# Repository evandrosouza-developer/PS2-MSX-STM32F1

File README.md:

# STM32: PS/2 to USB Converter

This code facilitates a STM32 chip to convert between PS/2 and MSX computer. It is meant to connect a keyboard, which only provides a PS/2 connector, to a MSX (or any one that have a up to 15 active columns and reads zeroes througth 8 bits - up to 15 x 8 matrix) computer.
This code powers and has been tested on the following Windows keyboards with brazilian 275 layout:
- Compaq RT235BTWBR;
- Clone KE11090749;
- Clone #09100.

The original code was originally developed based on:
- Cherry G80-3000LSMDE;

## Dependencies

- `arm-none-eabi-gcc`
- `arm-none-eabi-gdb`
- `arm-none-eabi-binutils`
- `arm-none-eabi-newlib`
- `stlink`
- `openocd (if you wnat to debug)`
- `mpfr`

## Preparations

After cloning the repository you need to make the following preparations:

```
git submodule init
git submodule update
cd libopencm3
make
cd ..
make
```

## Hardware and Setup

You will obviously need a STM32F103C8T6 chip. I have used a chinese blue pill. The software was made thinking in use of compatible processors, like GD32 for example. The software was made considering 8.000Mhz oscillator crystal, to clock the STM32F103C8T6 microcontroller chip at 72MHz. The connections are:

1) PS/2 Keyboard:
- Clock Pin PA12 - Connect to PS/2 mini-din 45322 pin 5 throught R16;
- Data Pin PA9 - Connect to PS/2 mini-din pin 1 throught R18;
- +5V PS/2 power - Connect collector of Q2 to mini-din pin 4;
- GND - Connect GNDD (Digital Ground) to mini-din pin 3.

2) MSX computer:
Obs.: You have to access PPI Ports B0 to B7 (Lines X0 to X7), Port C0 to C3 (Y0 to Y3), Port C6 (Caps Lock, pin 11 of DIP package), and for Russian and Japanese Computers (Cyrillic and Kana alphabets), you have to get access to YM2149 IOB7, pin 6 of DIP package.
- Y3 - Connect to MSX PPI 8255 Signal PC3;
- Y2 - Connect to MSX PPI 8255 Signal PC2;
- Y1 - Connect to MSX PPI 8255 Signal PC1;
- Y0 - Connect to MSX PPI 8255 Signal PC0;
- X7 - Connect to MSX PPI 8255 Signal PB7 (Hotbit HB-8000 CI-15 Pin 25);
- X6 - Connect to MSX PPI 8255 Signal PB6 (Hotbit HB-8000 CI-15 Pin 24);
- X5 - Connect to MSX PPI 8255 Signal PB5 (Hotbit HB-8000 CI-15 Pin 23);
- X4 - Connect to MSX PPI 8255 Signal PB4 (Hotbit HB-8000 CI-15 Pin 22);
- X3 - Connect to MSX PPI 8255 Signal PB3 (Hotbit HB-8000 CI-15 Pin 21);
- X2 - Connect to MSX PPI 8255 Signal PB2 (Hotbit HB-8000 CI-15 Pin 20);
- X1 - Connect to MSX PPI 8255 Signal PB1 (Hotbit HB-8000 CI-15 Pin 19);
- X0 - Connect to MSX PPI 8255 Signal PB0 (Hotbit HB-8000 CI-15 Pin 18);
- Caps LED - Connect to MSX PPI 8255 Signal PC6 (Hotbit HB-8000 CI-15 Pin 11 / Expert XP-800 CI-4);
- Kana LED - Connect to MSX YM2149 IOB7, pin 6 of DIP package. If the MSX doesn't have this, you can leave it open, as it already has an internal pull-up connection.

3) Serial connection: Needed only to update internal PS/2 to MSX key mapping Database. To create this Intel Hex file, better to use the Macro based Excel file, so you have to trust and enable macro excecution in excel app.
The structure of the Database is:
	The  three first columns of each line are the mapped scan codes;
	The 4th column is The Control Byte, detailed bellow:
	CONTROL BYTE:
		High nibble is Reserved;
		(bit 3) Combined Shift;
		(bit 2) Reserved-Not used;
		(bits 1-0) Modifyer Type:
		.0 - Default mapping
		.1 - NumLock Status+Shift changes
		.2 - PS/2 Shift
		.3 - Reserved-Not used
	
	This table has 3 modifyers: Up two MSX keys are considered to each mapping behavior modifying:
	
	5th and 6th columns have the mapping ".0 - Default mapping";
	7th e 8th columns have the mapping ".1 - NumLock Status+Shift changes";
	9th and 10th columns have the mapping ".2 - PS/2 Shift", where I need to
	release the sinalized Shift in PS/2 to the MSX and put the coded key, and so,
	release them, reapplying the Shift key, deppending on the initial state;

	Each column has a MSX coded key, with the sollwing structure:
	(Bit 7:4) MSX Y PPI 8255 PC3:0 is send to an OC outputs BCD decoder, for example:
					 In the case of Hotbit HB8000, the keyboard scan is done as a 9 columns scan, CI-16 7445N 08 to 00;
					 If equals to 1111 (Y=15), there is no MSX key mapped.
	(Bit 3)	 		 0: keypress
					 1: key release;
	(Bit 2:0) MSX X, ie, which bit will carry the key, to be read by PPI 8255 PB7:0.

Use a ST-Link v2 Programmer (or similar) to flash the program using `make flash` onto the STM32.

# PS2-MSX-STM32F1
# PS2-MSX-STM32F1

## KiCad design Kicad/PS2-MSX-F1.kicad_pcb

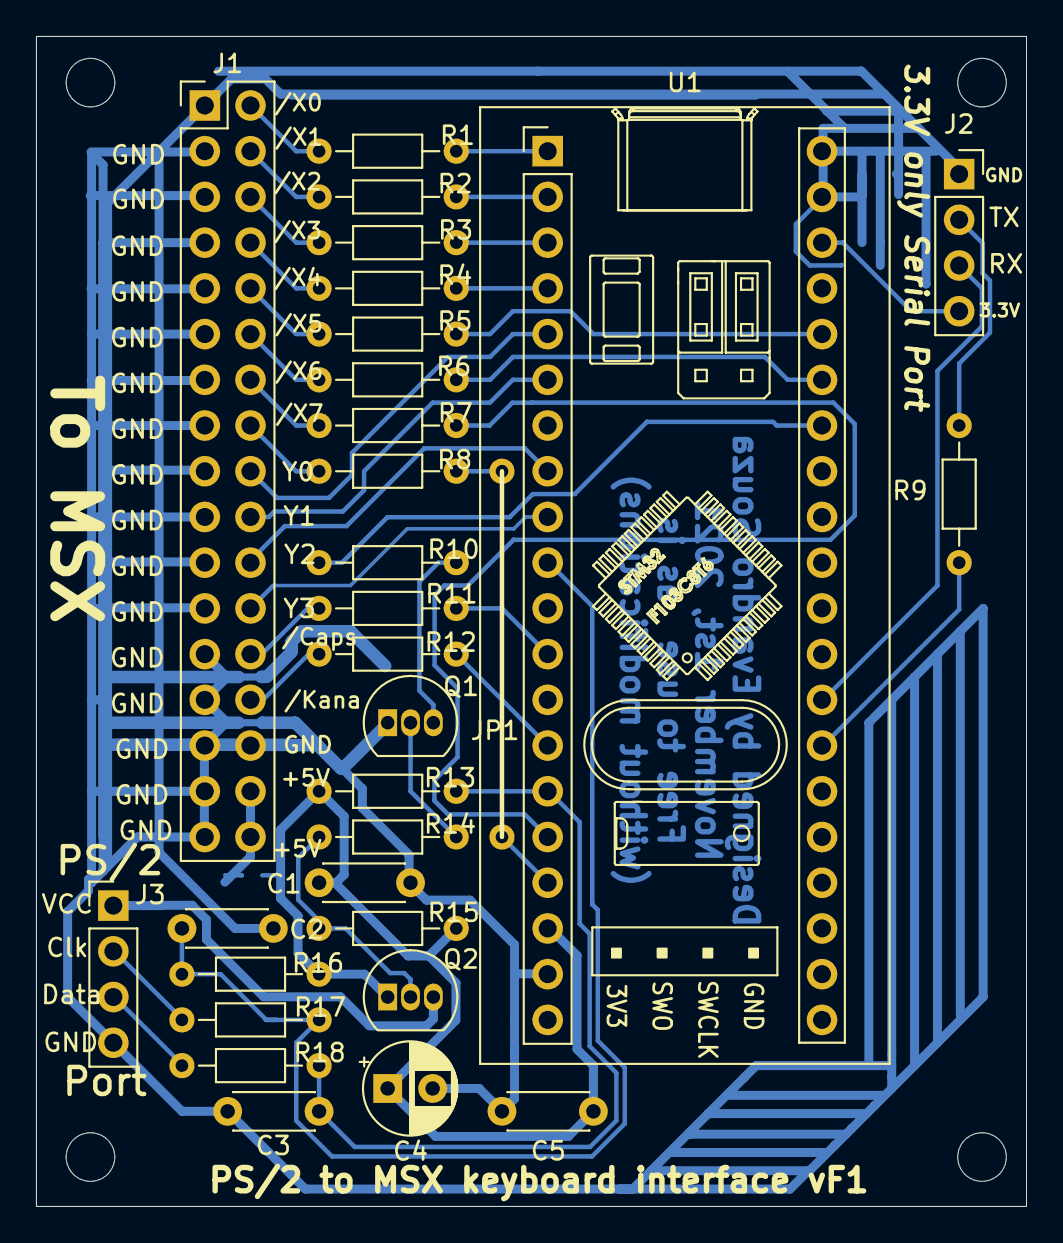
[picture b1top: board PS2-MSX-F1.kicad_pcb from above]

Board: 2 copper layers, 55.0 x 65.0 mm, 31 parts (1 on the bottom side), 41 nets.

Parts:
C1, C5: 100nF; C_Disc_D4.3mm_W1.9mm_P5.00mm
C2, C3: 220pF; C_Disc_D4.3mm_W1.9mm_P5.00mm
C4: 47uF x 10V; CP_Radial_D5.0mm_P2.50mm
F1: Poly Fuse 300mA SMD 0603 or 1206; Fuse_1206_0603_3216Metric_Pad1.42x1.75mm_HandSolder
J1: Conn_02x17_Odd_Even; PinHeader_2x17_P2.54mm_Vertical
J2: Conn_01x04; PinSocket_1x04_P2.54mm_Vertical
J3: Conn_01x04; PinHeader_1x04_P2.54mm_Vertical
JP1: .01; SolderWire-0.25sqmm_1x01_D0.65mm_OD1.7mm_Relief.kicad_SM2000
Q1: 2SC1815; TO-92_Inline
Q2: 2N2907; TO-92_Inline
R1, R2, R3, R4, R5, R6, R7, R8, R9, R17, R18: 22R; R_Axial_DIN0204_L3.6mm_D1.6mm_P7.62mm_Horizontal
R10, R14: 33K; R_Axial_DIN0204_L3.6mm_D1.6mm_P7.62mm_Horizontal
R11, R12, R13, R16: 10K; R_Axial_DIN0204_L3.6mm_D1.6mm_P7.62mm_Horizontal
R15: 150K; R_Axial_DIN0204_L3.6mm_D1.6mm_P7.62mm_Horizontal
U1: STM32F103C6T6 BluePill; BluePill_1

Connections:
+3V3: J2.4, U1.38
+5VD: C1.1, C4.1, C5.1, F1.1, Q2.1, R13.1, R15.1, R16.1, U1.18
/3.3V_Serial_RX: J2.3, U1.28
/3.3V_Serial_TX: J2.2, R9.1
/+5V_PS2_Keyboard: J3.1, Q2.3
/CapsL: R11.1, U1.12
/CapsLed: J1.26, R11.2
/KanaL: R12.1, U1.14
/KanaLed: J1.28, R12.2
/PS2Clk: C2.1, R16.2, R17.1, U1.10
/PS2ClkPin: J3.2, R17.2
/PS2Data: C3.1, R13.2, R18.1, U1.15
/PS2DataPin: J3.3, R18.2
/X0: J1.2, R1.1
/X0': R1.2, U1.1
/X1: J1.4, R2.1
/X1': R2.2, U1.2
/X2: J1.6, R3.1
/X2': R3.2, U1.3
/X3: J1.8, R4.1
/X3': R4.2, U1.4
/X4: J1.10, R5.1
/X4': R5.2, U1.36
/X5: J1.12, R6.1
/X5': R6.2, U1.35
/X6: J1.14, R7.1
/X6': R7.2, U1.16
/X7: J1.16, R8.1
/X7': JP1.2, U1.17
/Y0: J1.18, U1.5
/Y1: J1.20, U1.6
/Y2: J1.22, U1.8
/Y3: J1.24, U1.9
GNDD: C1.2, C2.2, C3.2, C4.2, C5.2, J1.1, J1.3, J1.5, J1.7, J1.9, J1.11, J1.13, J1.15, J1.17, J1.19, J1.21, J1.23, J1.25, J1.27, J1.29, J1.30, J1.31, J1.33, J2.1, J3.4, Q1.1, U1.19, U1.39, U1.40
unnamed: F1.2, J1.32, J1.34
unnamed: JP1.1, R8.2
unnamed: Q1.2, R14.2
unnamed: Q1.3, R10.1
unnamed: Q2.2, R14.1, R15.2
unnamed: R9.2, U1.27
unnamed: R10.2, U1.34

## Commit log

2021-11-18 November 18th upgrade - On going project
2021-11-18 Delete PS2toMSX-BR Mapping210715.xlsm
    Replaced to an updated file
2021-11-18 Updated versoin of Database generator
    This version fixes some keys wrong assignments.
2021-11-18 Updated port definitions
    Updated port definitions, reflecting Kicad schematics and PCB.
2021-11-18 Kicad files - Schematics and PCB
2021-12-08 Delete IEDBase.hex
    Newer file uploaded
2021-12-08 Delete PS2toMSX-BR Mapping211024.xlsx
    Newer file version uploaded
2021-12-08 Database file and its source code
    This unit has a highly configurable capability, as it has an user updateable database, without need to recompile and upload a new code, to translate from PC keyboard to MSX. This excel file is the as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
